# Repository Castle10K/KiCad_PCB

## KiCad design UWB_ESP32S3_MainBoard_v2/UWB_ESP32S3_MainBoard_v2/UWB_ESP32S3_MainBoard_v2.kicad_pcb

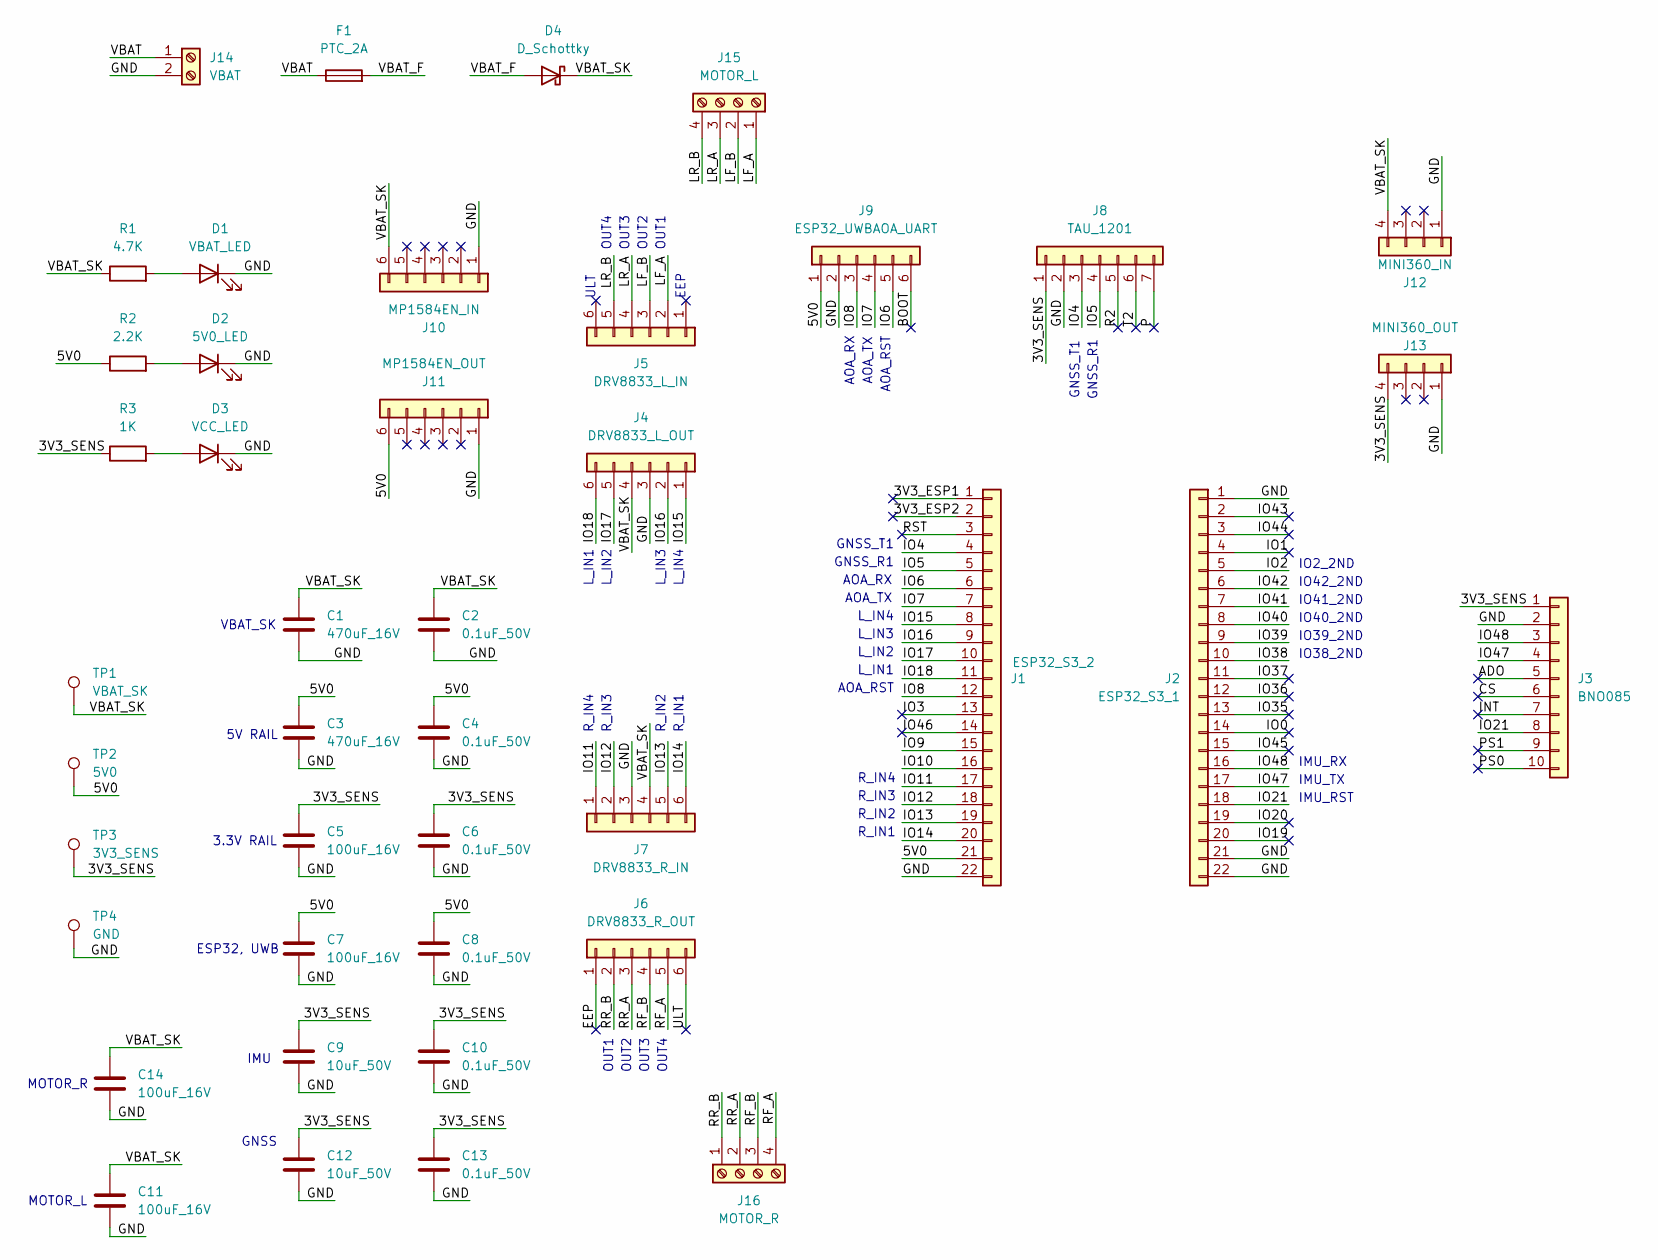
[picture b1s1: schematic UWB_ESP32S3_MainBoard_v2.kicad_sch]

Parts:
C1, C3: 470uF_16V; CP_Radial_D8.0mm_P3.50mm
C2, C4, C6, C8, C10, C13: 0.1uF_50V; C_0805_2012Metric_Pad1.18x1.45mm_HandSolder
C5, C7, C11, C14: 100uF_16V; CP_Radial_D5.0mm_P2.00mm
C9, C12: 10uF_50V; C_0805_2012Metric_Pad1.18x1.45mm_HandSolder
D1: VBAT_LED; LED_0805_2012Metric_Pad1.15x1.40mm_HandSolder
D2: 5V0_LED; LED_0805_2012Metric_Pad1.15x1.40mm_HandSolder
D3: VCC_LED; LED_0805_2012Metric_Pad1.15x1.40mm_HandSolder
D4: D_Schottky; D_SMA_Handsoldering
F1: PTC_2A; PTC_Radial_Disc_P5.08mm_Drill1.0mm
J1: ESP32_S3_2; PinSocket_1x22_P2.54mm_Vertical
J2: ESP32_S3_1; PinSocket_1x22_P2.54mm_Vertical
J3: BNO085; PinSocket_1x10_P2.54mm_Vertical
J4: DRV8833_L_OUT; PinSocket_1x06_P2.54mm_Vertical
J5: DRV8833_L_IN; PinSocket_1x06_P2.54mm_Vertical
J6: DRV8833_R_OUT; PinSocket_1x06_P2.54mm_Vertical
J7: DRV8833_R_IN; PinSocket_1x06_P2.54mm_Vertical
J8: TAU_1201; PinSocket_1x07_P2.54mm_Vertical
J9: ESP32_UWBAOA_UART; JST_XH_B6B-XH-A_1x06_P2.50mm_Vertical
J10: MP1584EN_IN; PinSocket_1x06_P2.54mm_Vertical
J11: MP1584EN_OUT; PinSocket_1x06_P2.54mm_Vertical
J12: MINI360_IN; PinSocket_1x04_P2.54mm_Vertical
J13: MINI360_OUT; PinSocket_1x04_P2.54mm_Vertical
J14: VBAT; KF301_2P_5.00mm
J15: MOTOR_L; KF301_4P_5.00mm
J16: MOTOR_R; KF301_4P_5.00mm
R1: 4.7K; R_0805_2012Metric_Pad1.20x1.40mm_HandSolder
R2: 2.2K; R_0805_2012Metric_Pad1.20x1.40mm_HandSolder
R3: 1K; R_0805_2012Metric_Pad1.20x1.40mm_HandSolder
TP1: VBAT_SK; TestPoint_Pad_D2.0mm
TP2: 5V0; TestPoint_Pad_D2.0mm
TP3: 3V3_SENS; TestPoint_Pad_D2.0mm
TP4: GND; TestPoint_Pad_D2.0mm

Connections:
/3V3_ESP1: J1.1
/3V3_ESP2: J1.2
/3V3_SENS: C5.1, C6.1, C9.1, C10.1, C12.1, C13.1, J3.1, J8.1, J13.4, R3.1, TP3.1 (1_1)
/5V0: C3.1, C4.1, C7.1, C8.1, J1.21, J9.1, J11.6, R2.1, TP2.1 (1_1)
/ADO: J3.5
/BOOT: J9.6
/CS: J3.6
/EEP: J6.1
/GND: C1.2, C2.2, C3.2, C4.2, C5.2, C6.2, C7.2, C8.2, C9.2, C10.2, C11.2, C12.2, C13.2, C14.2, D1.1 (K), D2.1 (K), D3.1 (K), J1.22, J2.1, J2.21, J2.22, J3.2, J4.3, J7.3, J8.2, J9.2, J10.1, J11.1, J12.1, J13.1, J14.2, TP4.1 (1_1)
/INT: J3.7
/IO0: J2.14
/IO1: J2.4
/IO2: J2.5
/IO3: J1.13
/IO4: J1.4, J8.3
/IO5: J1.5, J8.4
/IO6: J1.6, J9.5
/IO7: J1.7, J9.4
/IO8: J1.12, J9.3
/IO9: J1.15
/IO10: J1.16
/IO11: J1.17, J7.1
/IO12: J1.18, J7.2
/IO13: J1.19, J7.5
/IO14: J1.20, J7.6
/IO15: J1.8, J4.1
/IO16: J1.9, J4.2
/IO17: J1.10, J4.5
/IO18: J1.11, J4.6
/IO19: J2.20
/IO20: J2.19
/IO21: J2.18, J3.8
/IO35: J2.13
/IO36: J2.12
/IO37: J2.11
/IO38: J2.10
/IO39: J2.9
/IO40: J2.8
/IO41: J2.7
/IO42: J2.6
/IO43: J2.2
/IO44: J2.3
/IO45: J2.15
/IO46: J1.14
/IO47: J2.17, J3.4
/IO48: J2.16, J3.3
/LF_A: J5.2, J15.1
/LF_B: J5.3, J15.2
/LR_A: J5.4, J15.3
/LR_B: J5.5, J15.4
/P: J8.7
/PS0: J3.10
/PS1: J3.9
/R2: J8.5
/RF_A: J6.5, J16.4
/RF_B: J6.4, J16.3
/RR_A: J6.3, J16.2
/RR_B: J6.2, J16.1
/RST: J1.3
/T2: J8.6
/ULT: J6.6
/VBAT: F1.1, J14.1
/VBAT_F: D4.2 (A), F1.2
/VBAT_SK: C1.1, C2.1, C11.1, C14.1, D4.1 (K), J4.4, J7.4, J10.6, J12.4, R1.1, TP1.1 (1_1)
unnamed: D1.2 (A), R1.2
unnamed: D2.2 (A), R2.2
unnamed: D3.2 (A), R3.2

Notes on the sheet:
VBAT_SK
R_IN2
R_IN3
OUT4
L_IN4
R_IN4
EEP
OUT1
L_IN1
IMU
AOA_RST
GNSS_T1
IMU_TX
IO40_2ND
IMU_RST
AOA_TX
OUT2
GNSS_R1
IO2_2ND
L_IN3
L_IN2
R_IN1
IMU_RX
AOA_RX
IO39_2ND
IO41_2ND
IO42_2ND
IO38_2ND
MOTOR_L
OUT3
GNSS
ESP32, UWB
ULT
MOTOR_R
3.3V RAIL
5V RAIL

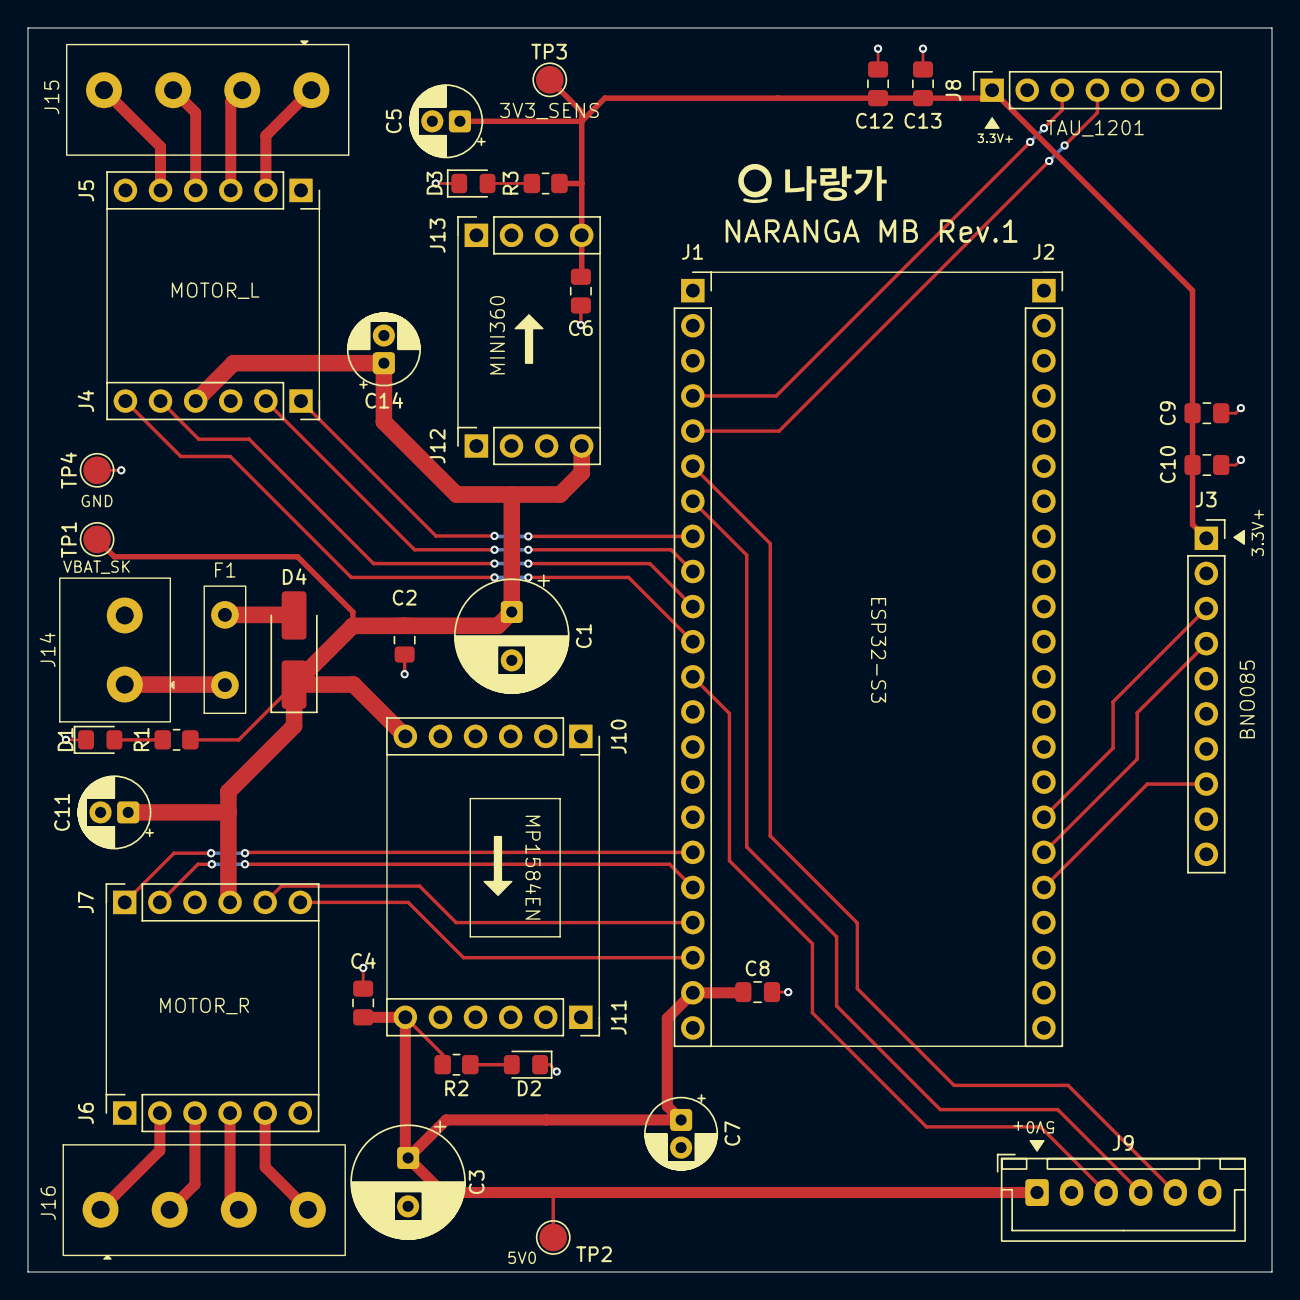
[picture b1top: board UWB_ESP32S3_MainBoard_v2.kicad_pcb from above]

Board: 2 copper layers, 90.0 x 90.0 mm, 42 parts (0 on the bottom side), 33 nets.

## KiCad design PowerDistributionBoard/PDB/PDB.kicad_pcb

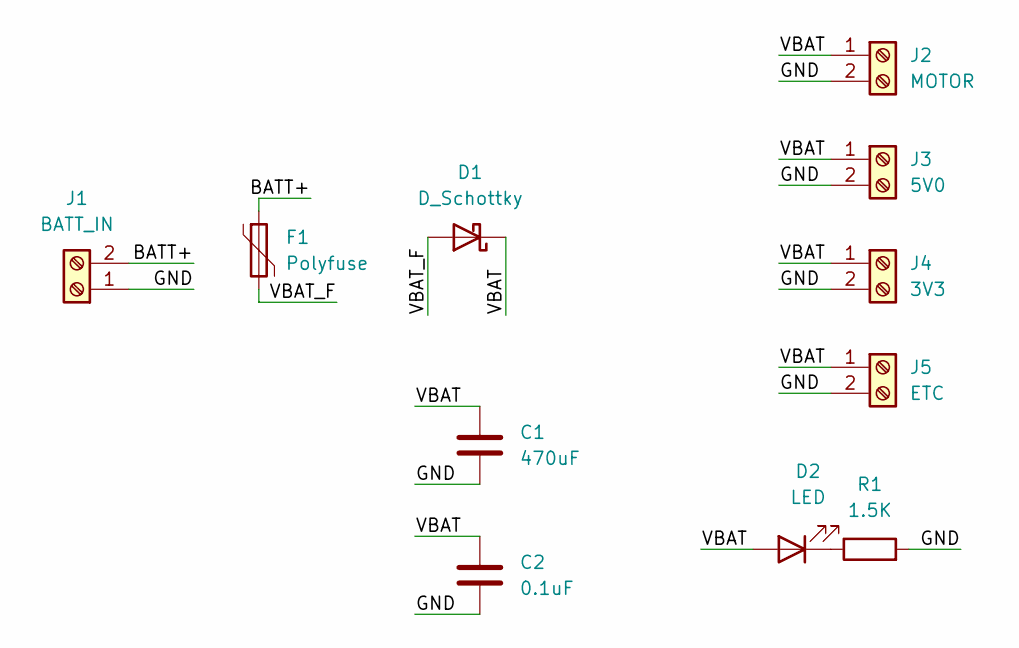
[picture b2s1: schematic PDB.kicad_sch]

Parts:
C1: 470uF; C_Radial_D8.0mm_H11.5mm_P3.50mm
C2: 0.1uF; C_0805_2012Metric_Pad1.18x1.45mm_HandSolder
D1: D_Schottky; D_SMA_Handsoldering
D2: LED; LED_0805_2012Metric_Pad1.15x1.40mm_HandSolder
F1: Polyfuse; PTC_Radial_Disc_P5.08mm_Drill1.0mm
J1: BATT_IN; KF301_2P_5.00mm
J2: MOTOR; KF301_2P_5.00mm
J3: 5V0; KF301_2P_5.00mm
J4: 3V3; KF301_2P_5.00mm
J5: ETC; KF301_2P_5.00mm
R1: 1.5K; R_0805_2012Metric_Pad1.20x1.40mm_HandSolder

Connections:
/BATT+: F1.1, J1.2
/GND: C1.2, C2.2, J1.1, J2.2, J3.2, J4.2, J5.2, R1.2
/VBAT: C1.1, C2.1, D1.1 (K), D2.2 (A), J2.1, J3.1, J4.1, J5.1
/VBAT_F: D1.2 (A), F1.2
unnamed: D2.1 (K), R1.1

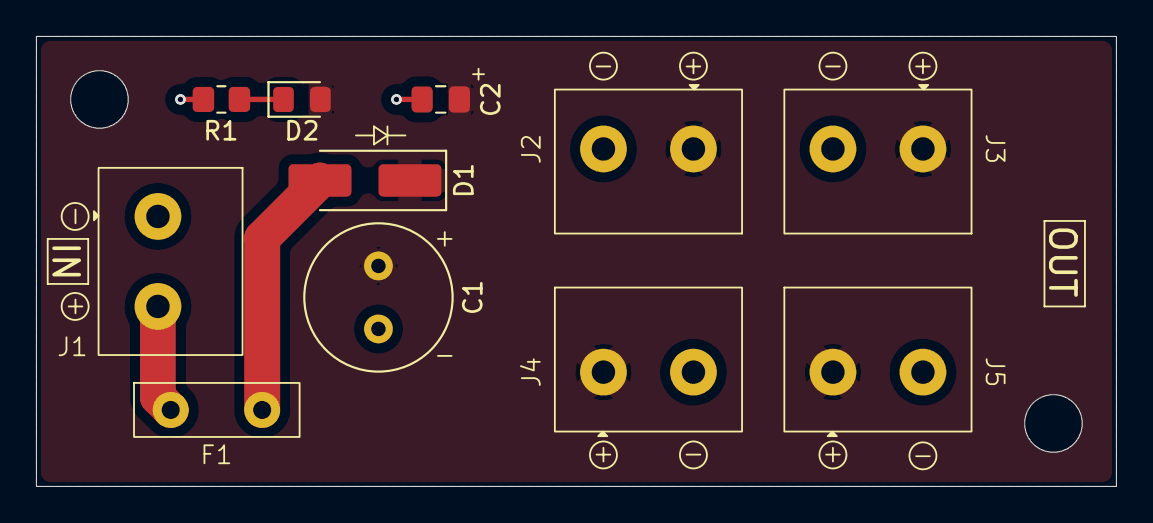
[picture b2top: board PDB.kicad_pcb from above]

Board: 2 copper layers, 60.0 x 25.0 mm, 13 parts (0 on the bottom side), 5 nets.

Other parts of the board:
M3, M3#2: MountingHole_3.2mm_M3

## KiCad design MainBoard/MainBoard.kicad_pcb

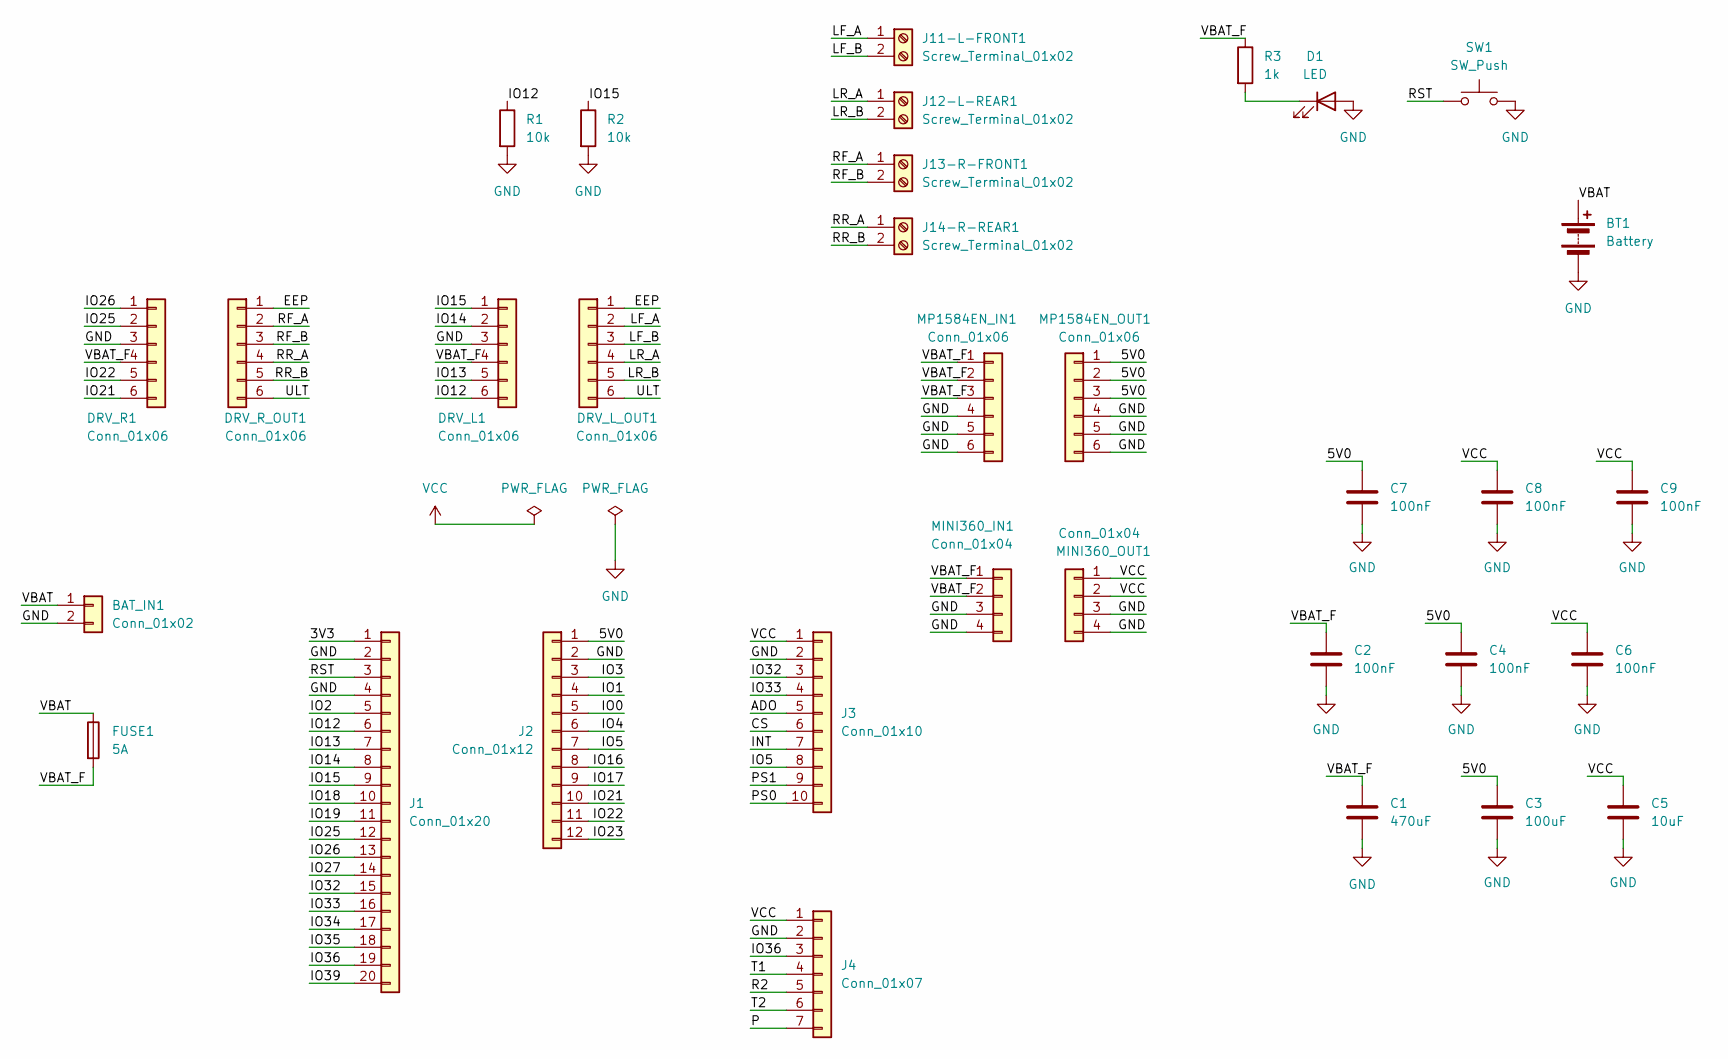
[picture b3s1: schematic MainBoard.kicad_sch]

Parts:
BAT_IN1: Conn_01x02; AMASS_XT30UPB-F_1x02_P5.0mm_Vertical
BT1: Battery
C1: 470uF; CP_Radial_D6.3mm_P2.50mm
C2, C4, C6, C7, C8, C9: 100nF; C_Disc_D5.0mm_W2.5mm_P5.00mm
C3: 100uF; CP_Radial_D6.3mm_P2.50mm
C5: 10uF; CP_Radial_D5.0mm_P2.50mm
D1: LED; LED_D5.0mm
DRV_L1: Conn_01x06; PinSocket_1x06_P2.54mm_Vertical
DRV_L_OUT1: Conn_01x06; PinSocket_1x06_P2.54mm_Vertical
DRV_R1: Conn_01x06; PinSocket_1x06_P2.54mm_Vertical
DRV_R_OUT1: Conn_01x06; PinSocket_1x06_P2.54mm_Vertical
FUSE1: 5A; Fuseholder_Cylinder-5x20mm_Schurter_0031_8201_Horizontal_Op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
J1: Conn_01x20; PinSocket_1x20_P2.54mm_Vertical
J2: Conn_01x12; PinSocket_1x12_P2.54mm_Vertical
J3: Conn_01x10; PinSocket_1x10_P2.54mm_Vertical
J4: Conn_01x07; PinSocket_1x07_P2.54mm_Vertical
J11-L-FRONT1, J12-L-REAR1, J13-R-FRONT1, J14-R-REAR1: Screw_Terminal_01x02; PhoenixContact_MSTBA_2,5_2-G-5,08_1x02_P5.08mm_Horizontal
MINI360_IN1, MINI360_OUT1: Conn_01x04; PinSocket_1x04_P2.54mm_Vertical
MP1584EN_IN1, MP1584EN_OUT1: Conn_01x06; PinSocket_1x06_P2.54mm_Vertical
R1, R2: 10k; R_Axial_DIN0204_L3.6mm_D1.6mm_P7.62mm_Horizontal
R3: 1k; R_Axial_DIN0204_L3.6mm_D1.6mm_P7.62mm_Horizontal
SW1: SW_Push; SW_PUSH_6mm

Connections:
/3V3: J1.1
/5V0: C3.1, C4.1, C7.1, J2.1, MP1584EN_OUT1.1, MP1584EN_OUT1.2, MP1584EN_OUT1.3
/ADO: J3.5
/CS: J3.6
/EEP: DRV_L_OUT1.1, DRV_R_OUT1.1
/INT: J3.7
/IO0: J2.5
/IO1: J2.4
/IO2: J1.5
/IO3: J2.3
/IO4: J2.6
/IO5: J2.7, J3.8
/IO12: DRV_L1.6, J1.6, R1.1
/IO13: DRV_L1.5, J1.7
/IO14: DRV_L1.2, J1.8
/IO15: DRV_L1.1, J1.9, R2.1
/IO16: J2.8
/IO17: J2.9
/IO18: J1.10
/IO19: J1.11
/IO21: DRV_R1.6, J2.10
/IO22: DRV_R1.5, J2.11
/IO23: J2.12
/IO25: DRV_R1.2, J1.12
/IO26: DRV_R1.1, J1.13
/IO27: J1.14
/IO32: J1.15, J3.3
/IO33: J1.16, J3.4
/IO34: J1.17
/IO35: J1.18
/IO36: J1.19, J4.3
/IO39: J1.20
/LF_A: DRV_L_OUT1.2, J11-L-FRONT1.1
/LF_B: DRV_L_OUT1.3, J11-L-FRONT1.2
/LR_A: DRV_L_OUT1.4, J12-L-REAR1.1
/LR_B: DRV_L_OUT1.5, J12-L-REAR1.2
/P: J4.7
/PS0: J3.10
/PS1: J3.9
/R2: J4.5
/RF_A: DRV_R_OUT1.2, J13-R-FRONT1.1
/RF_B: DRV_R_OUT1.3, J13-R-FRONT1.2
/RR_A: DRV_R_OUT1.4, J14-R-REAR1.1
/RR_B: DRV_R_OUT1.5, J14-R-REAR1.2
/RST: J1.3, SW1.1
/T1: J4.4
/T2: J4.6
/ULT: DRV_L_OUT1.6, DRV_R_OUT1.6
/VBAT: BAT_IN1.1, BT1.1 (+), FUSE1.1
/VBAT_F: C1.1, C2.1, DRV_L1.4, DRV_R1.4, FUSE1.2, MINI360_IN1.1, MINI360_IN1.2, MP1584EN_IN1.1, MP1584EN_IN1.2, MP1584EN_IN1.3, R3.1
GND: BAT_IN1.2, BT1.2 (-), C1.2, C2.2, C3.2, C4.2, C5.2, C6.2, C7.2, C8.2, C9.2, D1.2 (A), DRV_L1.3, DRV_R1.3, J1.2, J1.4, J2.2, J3.2, J4.2, MINI360_IN1.3, MINI360_IN1.4, MINI360_OUT1.3, MINI360_OUT1.4, MP1584EN_IN1.4, MP1584EN_IN1.5, MP1584EN_IN1.6, MP1584EN_OUT1.4, MP1584EN_OUT1.5, MP1584EN_OUT1.6, R1.2, R2.2, SW1.2
unnamed: D1.1 (K), R3.2
VCC: C5.1, C6.1, C8.1, C9.1, J3.1, J4.1, MINI360_OUT1.1, MINI360_OUT1.2

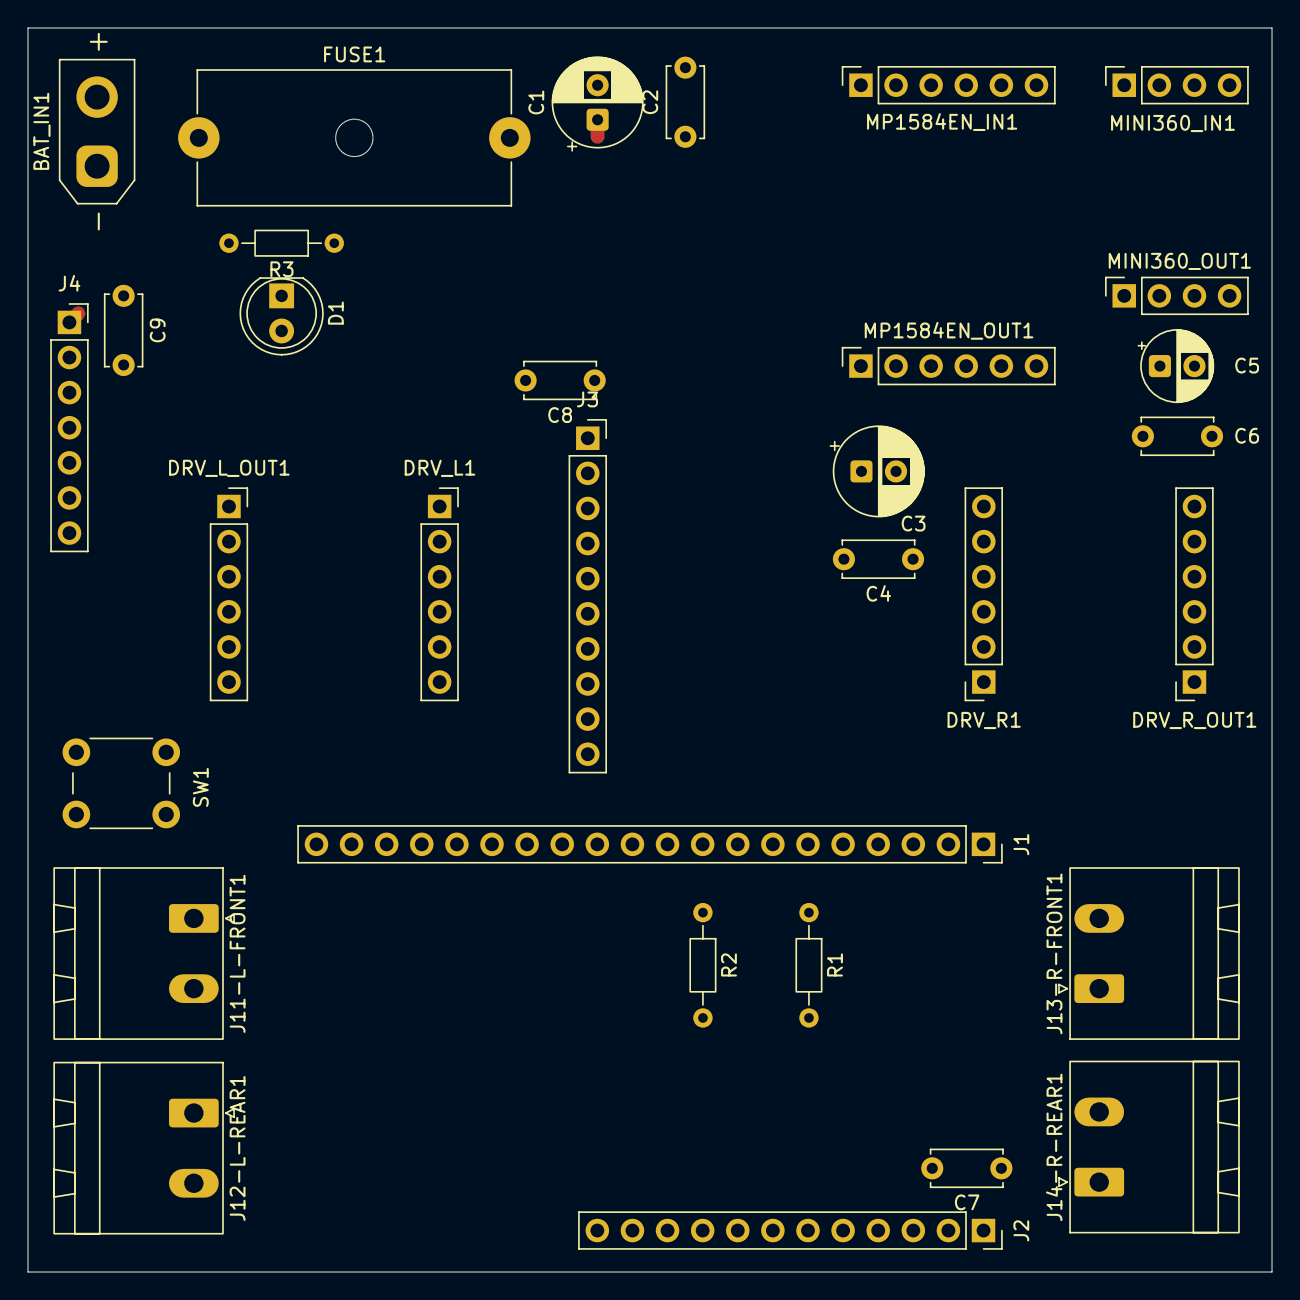
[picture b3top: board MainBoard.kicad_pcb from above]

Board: 2 copper layers, 90.0 x 90.0 mm, 32 parts (0 on the bottom side), 29 nets.

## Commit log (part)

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2026-05-08 KiCad esp32 12번핀에 저항 추가 전
2026-05-08 회로도 -> 풋프린트 완료 PCB편집기 제작 시작
2026-05-11 mini360_mp1584en회로수정
2026-05-14 전원배선완료
2026-05-14 drv8833_R배선필요
2026-05-21 PCB상 핀 배치가 짧고 편한 라우팅을 위해 핀맵 재설정 필요
2026-05-26 배선 삭제, 재배치 필요. 핀 넘버 정리
2026-05-28 ESP32_S3 칩 추가 분화
2026-05-29 PCB재설계
2026-06-02 esp32-s3 기반 pcb 배치 시작
2026-06-08 배치중1
2026-06-09 배치 완료, 풋프린트 추가 등
